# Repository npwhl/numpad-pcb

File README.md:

# 6x4 USB-C Numpad PCB
A PCB for a 6x4 numpad with a row for four customizable macros. Uses Alps switch footprints and a USB-C connection. Designed in Kicad.    

TBA: an image of the final PCB in person! :-)   
    
TBA: link to firmware repository   

# The Design
_A schematic of the MCU connections._  

_A schematic of the matrix of switch connections._    

_The front traces of the PCB._      

_The back traces of the PCB._      

# How It Was Made
**Software:** Kicad EDA v9.03  
**Manufacturer:** TBA  
This numpad uses the following bill of materials:    
| Designation | Type                   | Footprint | Quantity |
|-------------|------------------------|-----------|----------|
| FB1         | Ferrite Bead           | 0805      | 1        |
| SW1         | Reset switch           | SKQG      | 1        |
| SW2-SW23    | Reset switch           | ALPS      | 22       |
| C1-C4       | 100nF Capacitor        | 0805      | 4        |
| C5          | 10uF Capacitor         | 0805      | 1        |
| C6          | 1uF Capacitor          | 0805      | 1        |
| C7, C8      | 22pF Capacitor         | 0805      | 2        |
| R1, R2      | 10kΩ Resistor          | 0805      | 2        |
| R3, R4      | 22Ω Resistor           | 0805      | 2        |
| R5, R6      | 5.1kΩ Resistor         | 0805      | 2        |
| X1          | 16 MHz Crystal         | 3225      | 1        |
| USB1        | USB Connector          | HRO-TYPE-C-31-M-12 | 1  |
| U2          | PRTR5V0U2X             | SOT143B   | 1        |
| U1          | Atmega 32U4-AU         | TQFP-44   | 1        |
| F1          | PTC Fuse               | 1206      | 1        |
| D1-D23      | Diode                  | SOD-123   | 23       |      
   
The 3D modeling software Blender has many shortcuts that are only accessable using numpad shortcuts. Although these features are also accessable on Blender's UI, these shortcuts greatly accelerate the modeling process. However, my partner's keyboard is 65% and lacks a numpad. I wanted to design him a numpad that could solve this problem while using the keycaps and Alps switches he currently had. I also wanted to design the numpad with USB-C conectivity and a 4-key macro row for any additional shortcuts.  
  
To make the numpad, I followed [Masterzen's tutorial](https://www.masterzen.fr/2020/05/03/designing-a-keyboard-part-1/) on designing a PCB for a keyboard. This was my first time designing a PCB and using software like Kicad. I initially struggled with laying out the components on the PCB. I learned a lot of new information about why PCB components are laid out in specific ways and how to handle signals with minimal noise. I also learned about the importance of impedance on especially delicate routes such as the USB-C's D+/D- differential pair. In the future, I would like to optimize routing as much as possible with minimal vias. The amount of traces and their angles around the MCU are somewhat difficult to read and has the potential to create too much noise around the critical differential pairs. Since this is a low-speed numpad, this will most likely not be an issue, but I want to prioritize reliable PCB design moving forward.
      
_The PCB as viewed in the 3D viewer._      

# To Do
This PCB is still in progress. The next steps are:  
1. Order PCB board and its components. 
2. Program the firmware using [QMK](https://github.com/qmk/qmk_firmware). 
3. Model a chassis for the numpad in Solidworks. 
4. Create a main repository where the final design is kept. 

# How to Build
If you want to build the numpad yourself, you can order the parts following the links on the bill of materials table above! You can also use the same manufacturer, or the following Kicad-recommended manufacturers:  
* [Alsier (US)](https://aisler.net/)
* [OSHPark (US)](https://docs.oshpark.com/design-tools/kicad/generating-kicad-gerbers/)
* [PCBWay (China)](https://www.pcbway.com/blog/help_center/Generate_Gerber_file_from_Kicad.html)

<sub><sup>PS: Thank you (bf's github user)!</sup></sub>

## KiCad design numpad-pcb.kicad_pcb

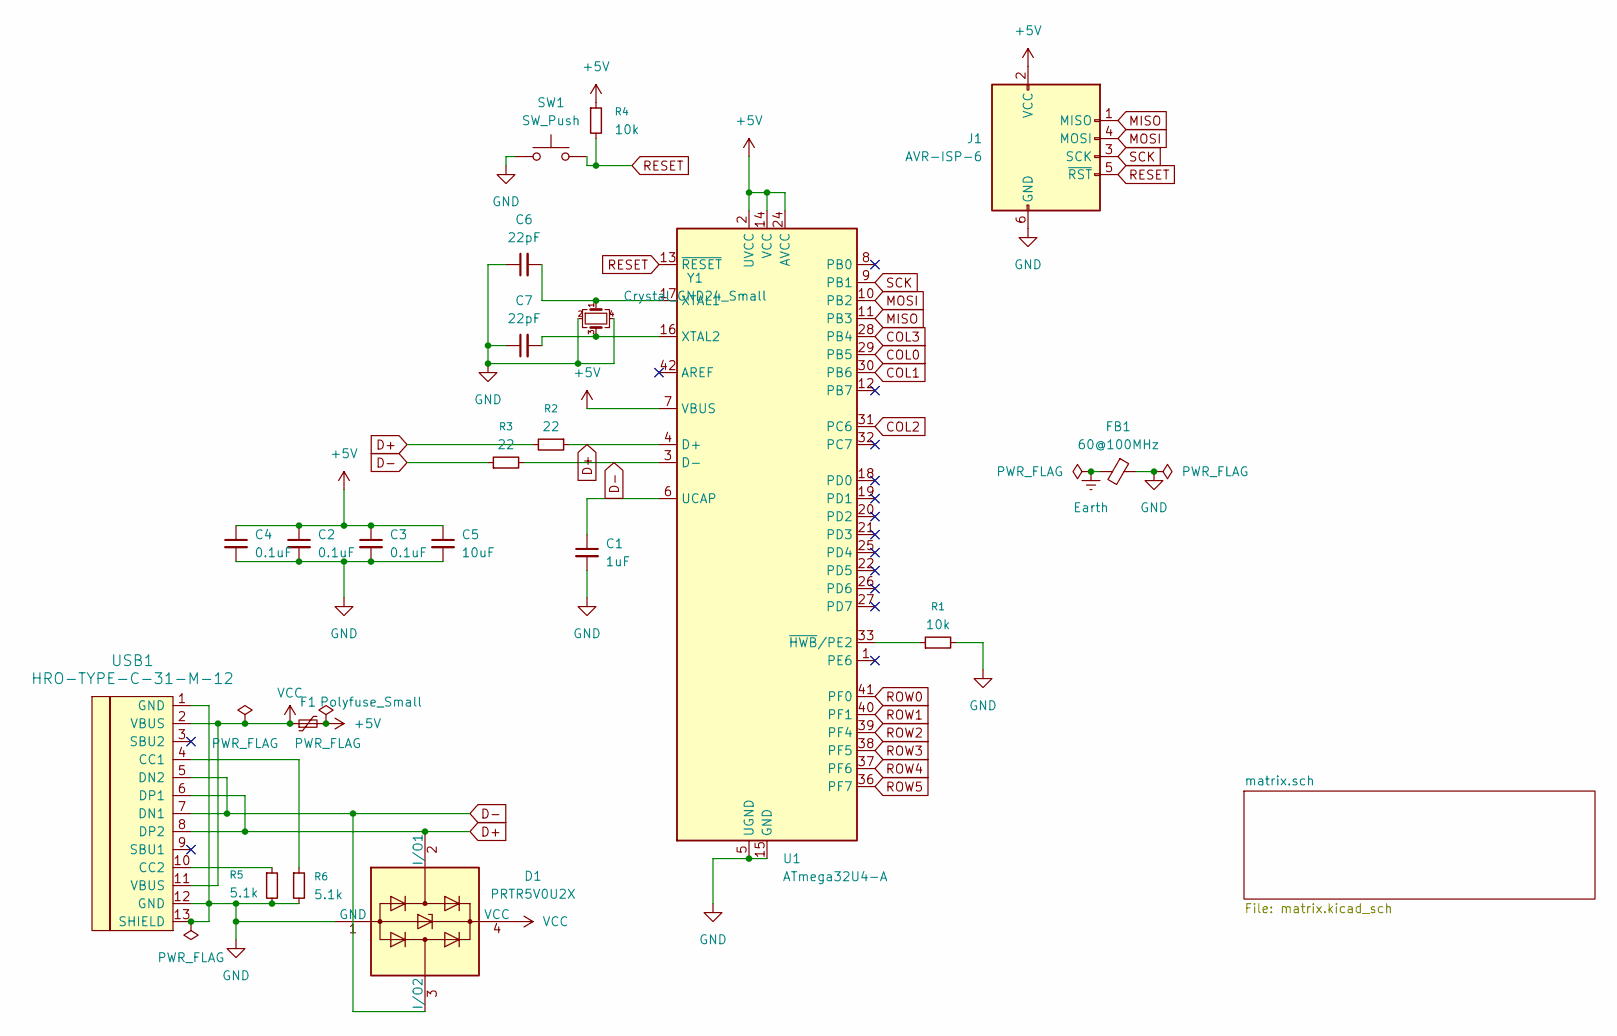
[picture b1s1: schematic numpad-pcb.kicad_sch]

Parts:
C1: 1uF; C_0805_2012Metric_Pad1.18x1.45mm_HandSolder
C2, C3, C4: 0.1uF; C_0805_2012Metric_Pad1.18x1.45mm_HandSolder
C5: 10uF; C_0805_2012Metric_Pad1.18x1.45mm_HandSolder
C6, C7: 22pF; C_0805_2012Metric_Pad1.18x1.45mm_HandSolder
D1: PRTR5V0U2X; SOT-143
F1: Polyfuse_Small; Fuse_1206_3216Metric_Pad1.42x1.75mm_HandSolder
FB1: 60@100MHz; L_0805_2012Metric_Pad1.15x1.40mm_HandSolder
J1: AVR-ISP-6; Reset_Pretty-Mask
R1, R4: 10k; R_0805_2012Metric_Pad1.20x1.40mm_HandSolder
R2, R3: 22; R_0805_2012Metric_Pad1.20x1.40mm_HandSolder
R5, R6: 5.1k; R_0805_2012Metric_Pad1.20x1.40mm_HandSolder
SW1: SW_Push; ALPS-1U
U1: ATmega32U4-A; TQFP-44_10x10mm_P0.8mm
USB1: HRO-TYPE-C-31-M-12; HRO-TYPE-C-31-M-12-HandSoldering
Y1: Crystal_GND24_Small; Crystal_SMD_3225-4Pin_3.2x2.5mm_HandSoldering

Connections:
+5V: C2.1, C3.1, C4.1, C5.1, F1.2, J1.2 (VCC), R4.1, U1.2 (UVCC), U1.7 (VBUS), U1.14 (VCC), U1.24 (AVCC), U1.34 (VCC), U1.44 (AVCC)
COL0: U1.29 (PB5); also elsewhere on the board
COL1: U1.30 (PB6); also elsewhere on the board
COL2: U1.31 (PC6); also elsewhere on the board
COL3: U1.28 (PB4); also elsewhere on the board
D+: D1.2 (I/O1), R2.1, R2.2, U1.4 (D+), USB1.6 (DP1), USB1.8 (DP2)
D-: D1.3 (I/O2), R3.1, R3.2, U1.3 (D-), USB1.5 (DN2), USB1.7 (DN1)
MISO: J1.1 (MISO), U1.11 (PB3)
MOSI: J1.4 (MOSI), U1.10 (PB2)
unnamed: C1.1, U1.6 (UCAP)
unnamed: C6.2, U1.17 (XTAL1), Y1.1
unnamed: C7.2, U1.16 (XTAL2), Y1.3
unnamed: R1.1, U1.33 (~HWB/PE2)
unnamed: R6.1, USB1.4 (CC1)
unnamed: R5.1, USB1.10 (CC2)
RESET: J1.5 (~RST), R4.2, SW1.2, U1.13 (~RESET)
ROW0: U1.41 (PF0); also elsewhere on the board
ROW1: U1.40 (PF1); also elsewhere on the board
ROW2: U1.39 (PF4); also elsewhere on the board
ROW3: U1.38 (PF5); also elsewhere on the board
ROW4: U1.37 (PF6); also elsewhere on the board
ROW5: U1.36 (PF7); also elsewhere on the board
SCK: J1.3 (SCK), U1.9 (PB1)
VCC: D1.4 (VCC), F1.1, USB1.2 (VBUS), USB1.11 (VBUS)

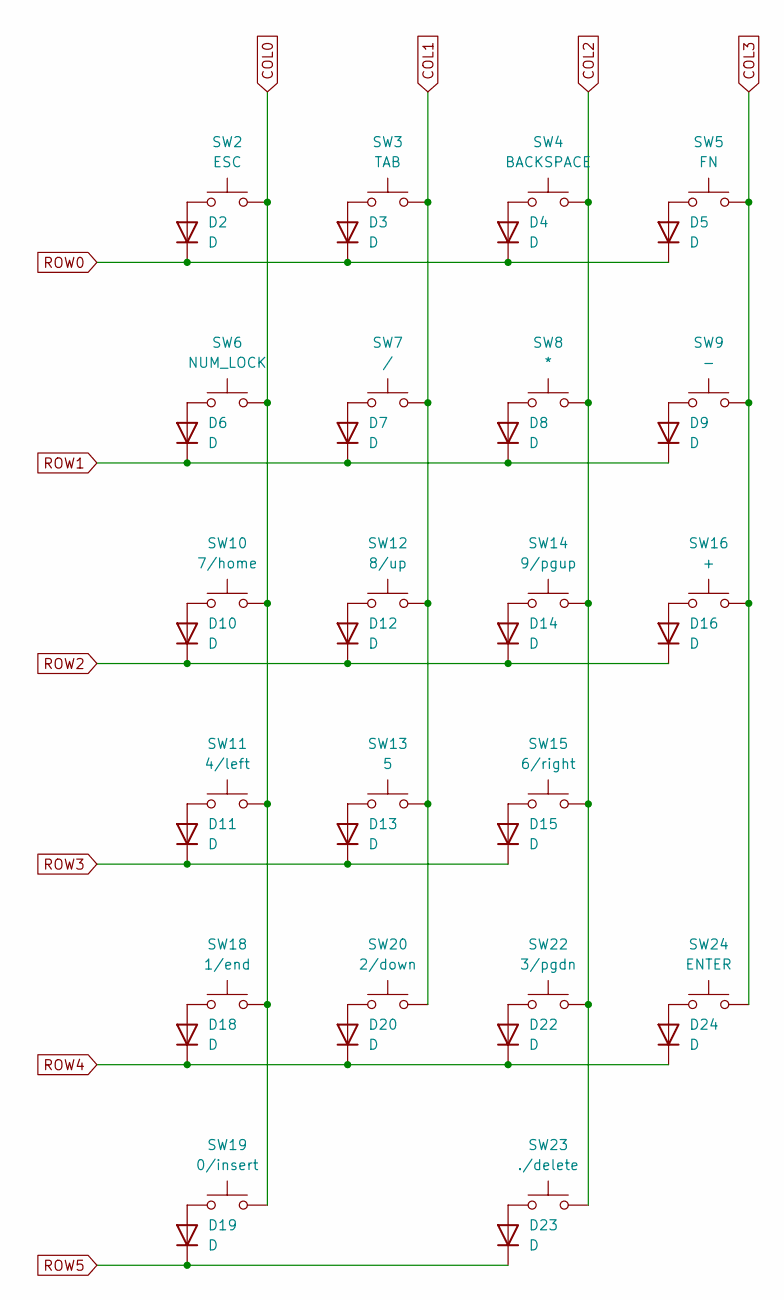
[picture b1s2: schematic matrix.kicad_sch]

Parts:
D2, D3, D4, D5, D6, D7, D8, D9, D10, D11, D12, D13, D14, D15, D16, D18, D19, D20, D22, D23, D24: D; D_SOD-123
SW2: ESC; ALPS-1U
SW3: TAB; ALPS-1U
SW4: BACKSPACE; ALPS-1U
SW5: FN; ALPS-1U
SW6: NUM_LOCK; ALPS-1U
SW7: /; ALPS-1U
SW8: *; ALPS-1U
SW9: -; ALPS-1U
SW10: 7/home; ALPS-1U
SW11: 4/left; ALPS-1U
SW12: 8/up; ALPS-1U
SW13: 5; ALPS-1U
SW14: 9/pgup; ALPS-1U
SW15: 6/right; ALPS-1U
SW16: +; ALPS-2U
SW18: 1/end; ALPS-1U
SW19: 0/insert; ALPS-2U
SW20: 2/down; ALPS-1U
SW22: 3/pgdn; ALPS-1U
SW23: ./delete; ALPS-1U
SW24: ENTER; ALPS-2U

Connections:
COL0: SW2.2, SW6.2, SW10.2, SW11.2, SW18.2, SW19.2; also elsewhere on the board
COL1: SW3.2, SW7.2, SW12.2, SW13.2, SW20.2; also elsewhere on the board
COL2: SW4.2, SW8.2, SW14.2, SW15.2, SW22.2, SW23.2; also elsewhere on the board
COL3: SW5.2, SW9.2, SW16.2, SW24.2; also elsewhere on the board
unnamed: D2.2 (A), SW2.1
unnamed: D3.2 (A), SW3.1
unnamed: D4.2 (A), SW4.1
unnamed: D5.2 (A), SW5.1
unnamed: D6.2 (A), SW6.1
unnamed: D7.2 (A), SW7.1
unnamed: D8.2 (A), SW8.1
unnamed: D9.2 (A), SW9.1
unnamed: D10.2 (A), SW10.1
unnamed: D11.2 (A), SW11.1
unnamed: D12.2 (A), SW12.1
unnamed: D13.2 (A), SW13.1
unnamed: D14.2 (A), SW14.1
unnamed: D15.2 (A), SW15.1
unnamed: D16.2 (A), SW16.1
unnamed: D18.2 (A), SW18.1
unnamed: D19.2 (A), SW19.1
unnamed: D20.2 (A), SW20.1
unnamed: D22.2 (A), SW22.1
unnamed: D23.2 (A), SW23.1
unnamed: D24.2 (A), SW24.1
ROW0: D2.1 (K), D3.1 (K), D4.1 (K), D5.1 (K); also elsewhere on the board
ROW1: D6.1 (K), D7.1 (K), D8.1 (K), D9.1 (K); also elsewhere on the board
ROW2: D10.1 (K), D12.1 (K), D14.1 (K), D16.1 (K); also elsewhere on the board
ROW3: D11.1 (K), D13.1 (K), D15.1 (K); also elsewhere on the board
ROW4: D18.1 (K), D20.1 (K), D22.1 (K), D24.1 (K); also elsewhere on the board
ROW5: D19.1 (K), D23.1 (K); also elsewhere on the board

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
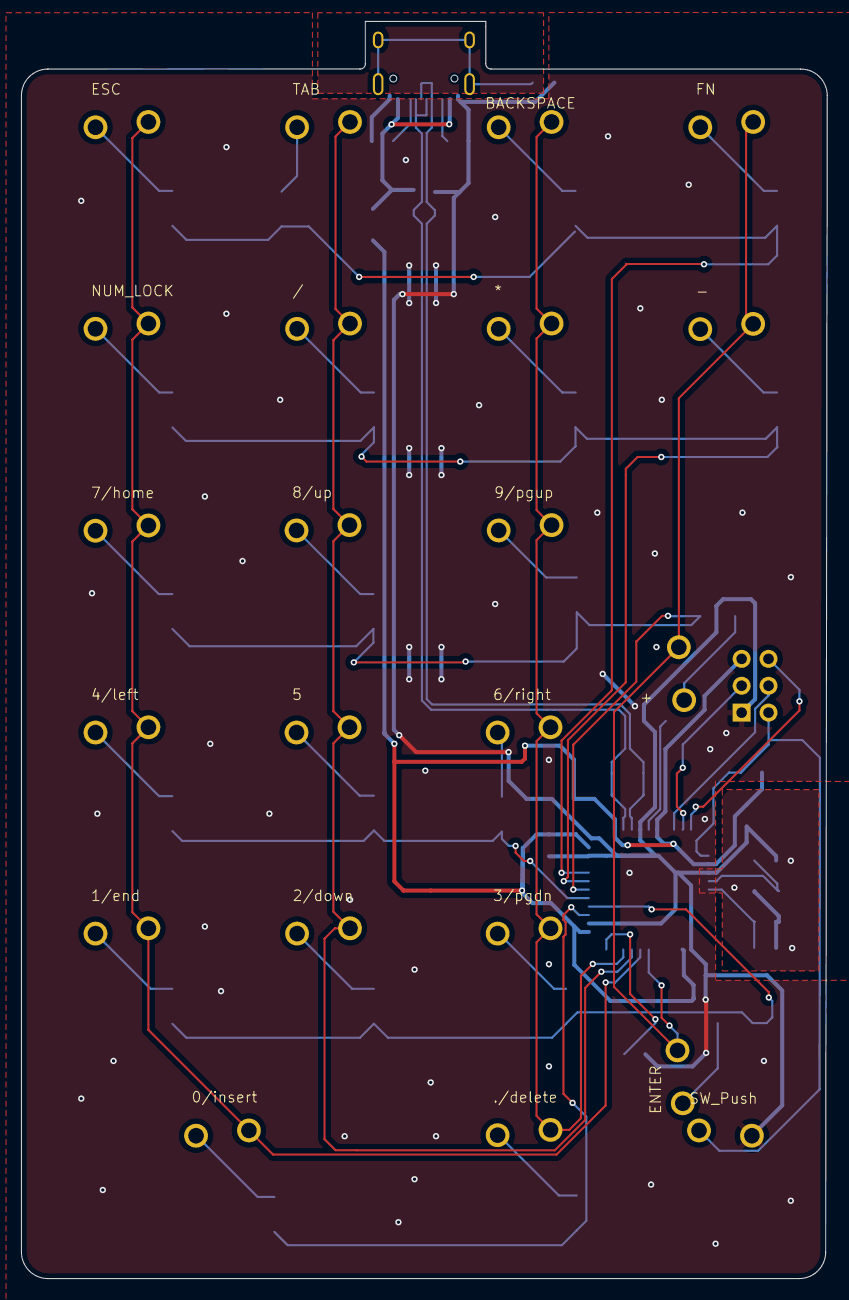
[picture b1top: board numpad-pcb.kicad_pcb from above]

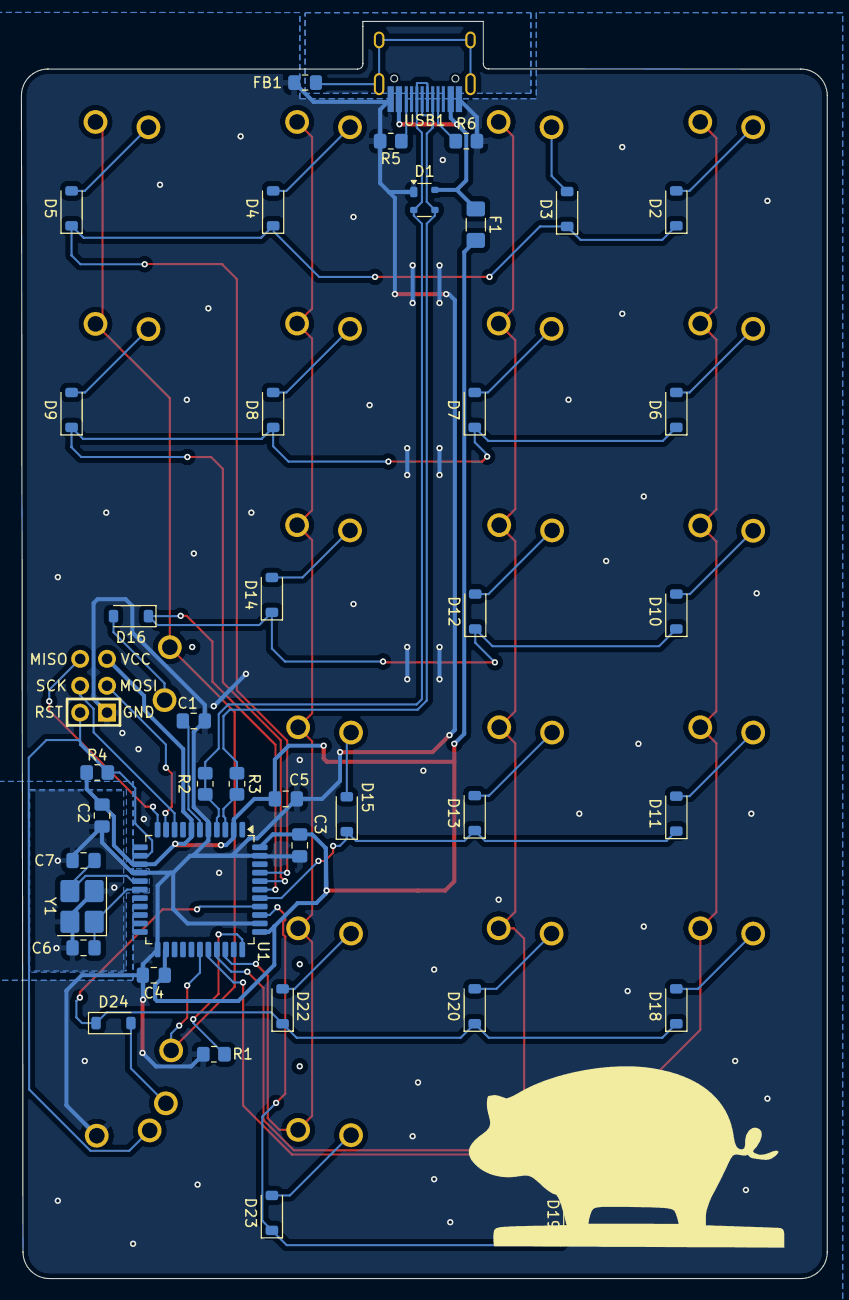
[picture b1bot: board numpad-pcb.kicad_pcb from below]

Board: 2 copper layers, 76.2 x 118.8 mm, 63 parts (42 on the bottom side), 47 nets.

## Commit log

2025-08-03 Add submodules
2025-08-03 Incude submodules in Kicad
2025-08-03 Complete MCU schematic
2025-08-06 Add USB-C submodule
2025-08-07 Add USB-C and reset schematic
2025-08-07 Create numpad matrix
2025-08-07 Fix schematic based on ERC
2025-08-13 Update PCB to show schematic changes
2025-08-13 Correct PCB footprints
2025-08-14 Initial layout of PCB components
2025-08-14 Fix silkscreen errors
2025-08-14 Update USB-C 3D model
2025-08-14 Repair edge and bottom traces
    Fixed the differential pair to have closer trace lengths (+/- 0.5 mm
    reduced to 0.03 mm) for higher accuracy and error prevention. Also
    created GND pour for crystal to reduce noise.
2025-08-14 Routed power
2025-08-15 Update README with images
2025-08-15 Resize README images
2025-08-15 Fix image captions in README
2025-08-15 Finish traces and start silkscreen
    Still need to modify traces to be more optimal and increase readibility.
    Also updated silkscreen preferences locally to have the label of each
    switch on both the front and back of the PCB. Need to make a note that
    this change is local because of the submodule imported from the start.
2025-08-15 Decorate PCB
2025-08-15 Add copper ground pour
2025-08-15 Restore schematic backup
2025-08-16 Add USB-C shield protection
    Changed the USB-C shield from being connected to ground to being
    connected to a ferrite bead low pass filter to manage ESD. Also adjusted
    ground around USB to prevent ESD from damaging nearby components.
